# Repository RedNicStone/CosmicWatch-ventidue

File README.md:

---

# CosmicWatch Ventidue
Continuation of the original CosmicWatch project by Spencer featuring many improvements and additions.

## What's new?
CosmicWatch Ventidue's new features are plentiful so here is a quick summary:
- Flexible design that allows connecting either one or two detectors
- Built in on-silicon coincidence detection between the two modules
  - Time resolutions from 5ns down to just 1ns [cooling required]
- Powerful Teensy 4.1 microcontroller
- Full color 1.5" OLED display with great user interface
  - Rotary encoder for easy navigation
  - Buzzer for audible counting and interface feedback
  - Custom rendering library for maximum performance
- Optional solder-free support for multiple prebuilt sensor modules
  - GPS, Pressure, Humidity, Temperature and RTC supported
- Built in Ethernet module for intra & intercommunication
- Improved mechanical stability and 3D printed casing
- Interrupt driven software architecture for accurate counting and a responsive user interface

## Hardware 
A first prototype has been produced and tested. 
We are currently busy on fabricating a newer board that will be tested as soon as finished.  
There are plans to provide a kit with a pre-assembled board for purchase once hardware development has sized.

### Overview
> todo

## Software 
Software is currently undergoing heavy development and is only barely runnable.  
If you do want to take a look [check this folder](software/arduino).

The following modules have been written so far:
- Custom rendering pipeline
- OLED driver [Needs push to support DMA]
- On-chip coincidence detection
- Example for testing peripherals

The following modules still need tending:
- True type font rendering
- UI and windowing system
- Data acquisition and storage
- Ethernet communication

**Any help is much appreciated!**

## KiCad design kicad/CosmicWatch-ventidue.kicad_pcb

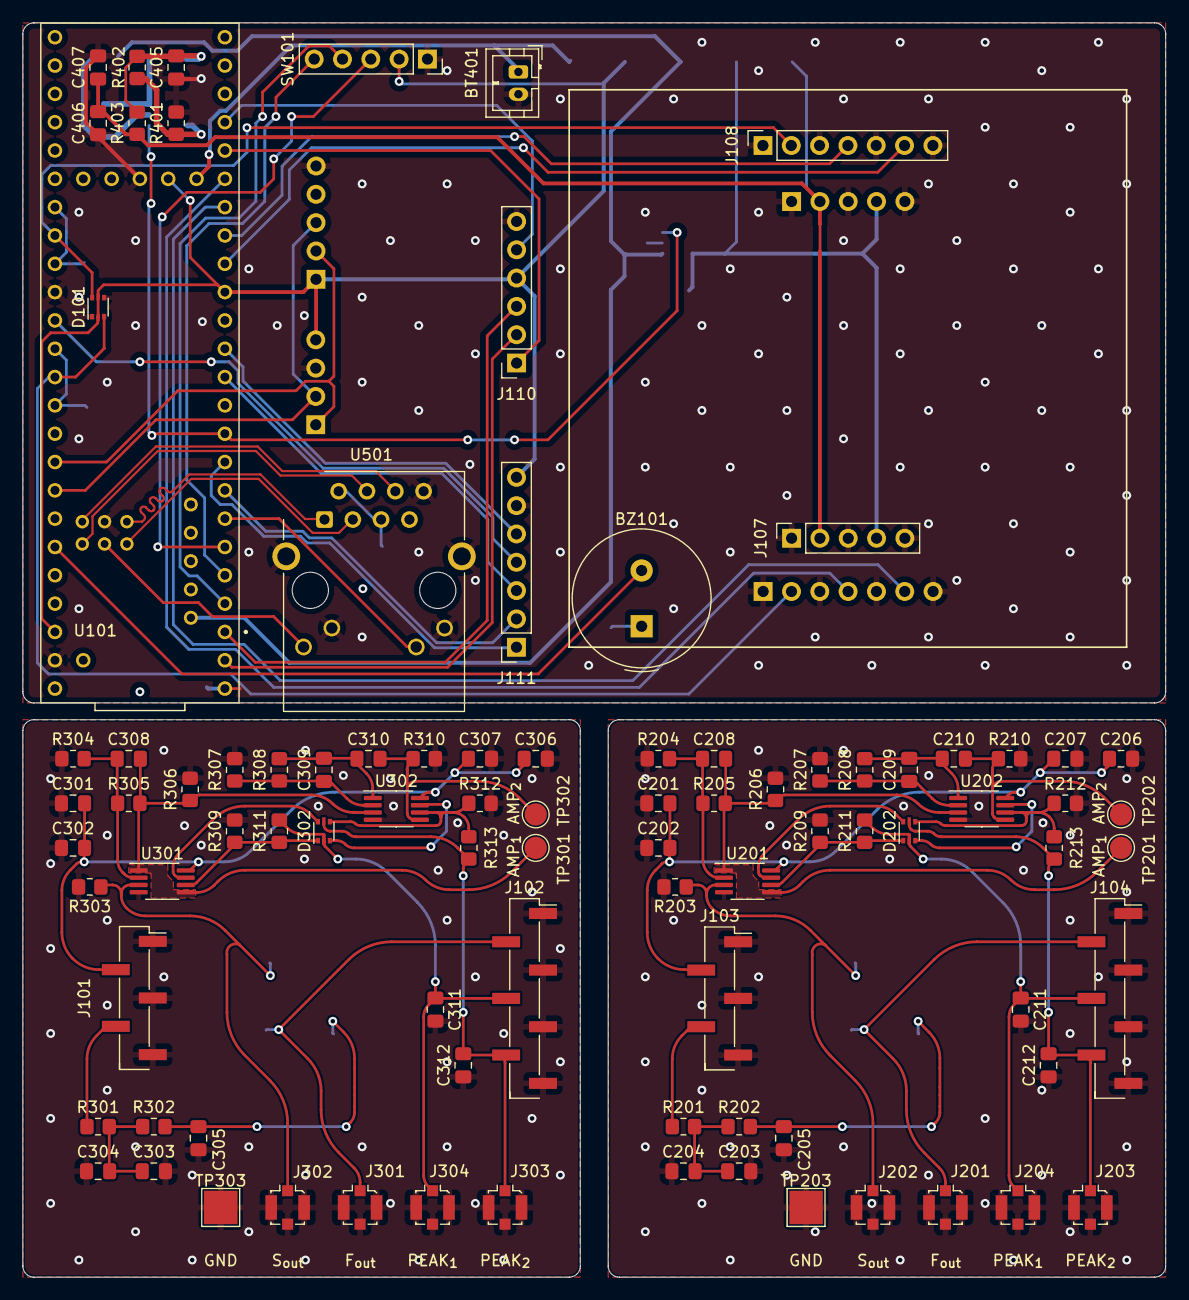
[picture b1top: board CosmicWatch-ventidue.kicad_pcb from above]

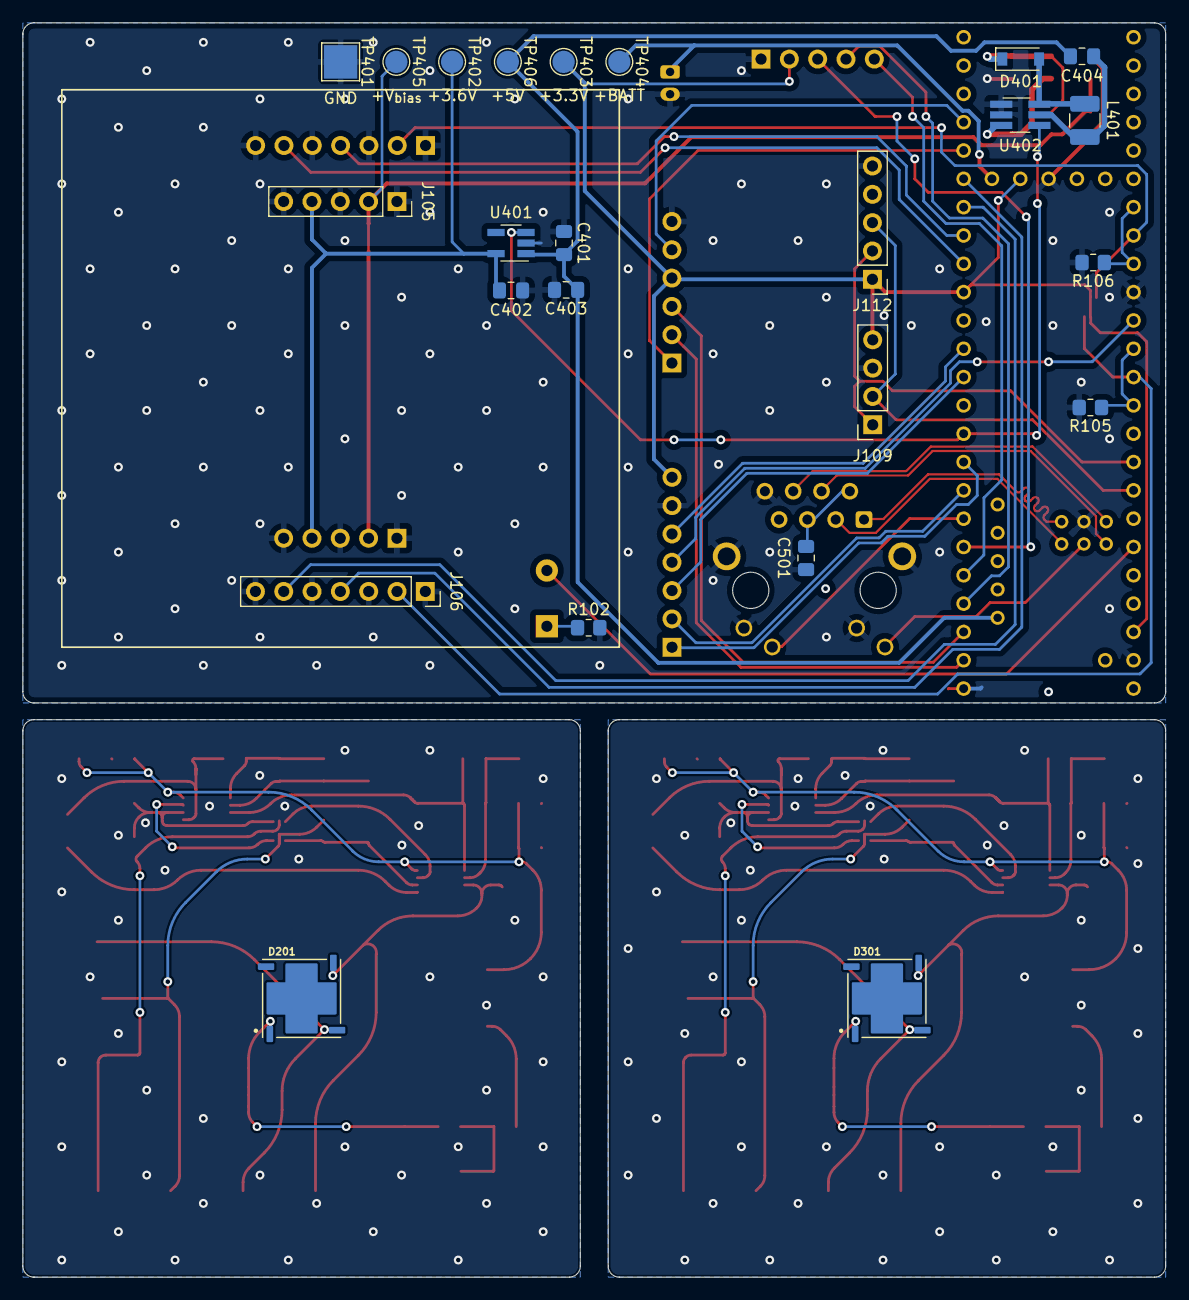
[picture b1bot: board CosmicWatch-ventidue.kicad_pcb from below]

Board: 2 copper layers, 102.5 x 112.5 mm, 114 parts (24 on the bottom side), 78 nets.

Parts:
BT401: Battery_Cell; JST_PH_B2B-PH-K_1x02_P2.00mm_Vertical
BZ101: Buzzer; Buzzer_TDK_PS1240P02BT_D12.2mm_H6.5mm
C201, C204, C205, C207, C301, C304, C305, C307, C407: 10nF; C_0805_2012Metric_Pad1.18x1.45mm_HandSolder
C202, C206, C302, C306, C501: 0.1uF; C_0805_2012Metric_Pad1.18x1.45mm_HandSolder
C203, C210, C303, C310, C401, C402, C403, C404, C405, C406: 1uF; C_0805_2012Metric_Pad1.18x1.45mm_HandSolder
C208, C209, C308, C309: 13pF; C_0805_2012Metric_Pad1.18x1.45mm_HandSolder
C211, C212, C311, C312: 2nF; C_0805_2012Metric_Pad1.18x1.45mm_HandSolder
D101, D202, D302: BAS70XY; SOT-666
D201, D301: SiPM_MICRORB−60035−MLP; SiPM_MICROFC-60035-SMT-HANDSOLDER
D401: D_Schottky; D_SOD-123
J101, J103: Conn_01x05; PinHeader_1x05_P2.54mm_Vertical_SMD_Pin1Right
J102, J104: Conn_01x07; PinHeader_1x07_P2.54mm_Vertical_SMD_Pin1Right
J105, J107: Conn_01x05; PinSocket_1x05_P2.54mm_Vertical
J106, J108: Conn_01x07; PinSocket_1x07_P2.54mm_Vertical
J109: BMP280; PinSocket_1x04_P2.54mm_Vertical
J110: Conn_01x06; PinSocket_1x06_P2.54mm_Vertical
J111: OLED; PinSocket_1x07_P2.54mm_Vertical
J112: DS3231; PinHeader_1x05_P2.54mm_Vertical
J201, J202, J203, J204, J301, J302, J303, J304: Conn_SMA; U.FL_Molex_MCRF_73412-0110_Vertical
L401: 47uH; L_1210_3225Metric_Pad1.42x2.65mm_HandSolder
R102, R208, R308: 1k; R_0805_2012Metric_Pad1.20x1.40mm_HandSolder
R105, R106, R206, R210, R306, R310: 10k; R_0805_2012Metric_Pad1.20x1.40mm_HandSolder
R201, R202, R301, R302: 50; R_0805_2012Metric_Pad1.20x1.40mm_HandSolder
R203, R303: 10; R_0805_2012Metric_Pad1.20x1.40mm_HandSolder
R204, R207, R304, R307: 150; R_0805_2012Metric_Pad1.20x1.40mm_HandSolder
R205, R305: 2.32k; R_0805_2012Metric_Pad1.20x1.40mm_HandSolder
R209, R211, R212, R213, R309, R311, R312, R313: 100k; R_0805_2012Metric_Pad1.20x1.40mm_HandSolder
R401: 6.65k; R_0805_2012Metric_Pad1.20x1.40mm_HandSolder
R402: 147k; R_0805_2012Metric_Pad1.20x1.40mm_HandSolder
R403: 100; R_0805_2012Metric_Pad1.20x1.40mm_HandSolder
SW101: Digital_Rotary_Encoder_Switch; PinSocket_1x05_P2.54mm_Vertical
TP201, TP301: AMP_{1}; TestPoint_Pad_D2.0mm
TP202, TP302: AMP_{2}; TestPoint_Pad_D2.0mm
TP203, TP303: GND; TestPoint_Pad_3.0x3.0mm
TP401: TestPoint; TestPoint_Pad_3.0x3.0mm
TP402, TP403, TP404, TP405, TP406: TestPoint; TestPoint_Pad_D2.0mm
U101: Teensy4.1
U201, U202, U301, U302: LT1807; MSOP-8_3x3mm_P0.65mm
U401: TCR2EF; SOT-23-5_HandSoldering
U402: MAX5025; TSOT-23-6_HandSoldering
U501: J1B12111CCD; RJ45_Cetus_J1B1211CCD_Horizontal

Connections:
+3.3V: D101.2 (K), D101.5 (K), J109.4, J110.4, J111.7, J112.1, SW101.2 (VCC), TP403.1, U101.3.3V_1 (3.3V), U101.3.3V_2 (3.3V__1), U101.3.3V_3 (3.3V__2)
+3.6V: C402.1, J105.4, J107.4, TP402.1, U401.5 (VOUT)
+5V: C401.1, C403.1, C404.1, TP406.1, U101.5V, U401.1 (VIN)
+BATT: BT401.1 (+), TP404.1, U101.VBAT
+V_{bias}: C406.1, C407.1, J105.2, J107.2, R403.2, TP405.1
/Buzzer: BZ101.2 (+), U101.21 (A7)
/D_{1}-F: D101.3 (common), J106.2, U101.15 (A1)
/D_{1}-P_{1}: J106.4, U101.27 (A13)
/D_{1}-P_{2}: J106.6, U101.26 (A12)
/D_{2}-F: D101.6 (common), J108.2, U101.40 (A16)
/D_{2}-P_{1}: J108.4, U101.25 (A11)
/D_{2}-P_{2}: J108.6, U101.24 (A10)
/Detector PCB 1/+3.6V: C301.1, C302.1, C306.1, C307.1, J101.2, U301.8 (V+), U302.8 (V+)
/Detector PCB 1/AMP_{1}: C308.2, R305.2, R306.1, TP301.1, U301.1, U301.5 (+), U302.3 (+)
/Detector PCB 1/AMP_{2}: C310.2, R310.1, TP302.1, U302.5 (+)
/Detector PCB 1/F_{out}: D301.2 (Fast_Output), J102.2, J301.1 (In)
/Detector PCB 1/GND: C301.2, C302.2, C303.2, C304.2, C305.2, C306.2, C307.2, C311.2, C312.2, J101.1, J101.3, J101.5, J102.1, J102.3, J102.5, J102.7, J301.2 (Ext), J302.2 (Ext), J303.2 (Ext), J304.2 (Ext), R303.2, R304.2, R306.2, R307.2, R309.2, R310.2, R312.2, TP303.1, U301.4 (V-), U302.4 (V-)
/Detector PCB 1/PEAK_{1}: C311.1, D302.2 (K), J102.4, J304.1 (In), R311.2
/Detector PCB 1/PEAK_{2}: C312.1, D302.5 (K), J102.6, J303.1 (In), R313.2
/Detector PCB 1/S_{out}: D301.3 (Cathode), J302.1 (In), R303.1, U301.3 (+)
/Detector PCB 1/V_{bias}: J101.4, R301.1
/Detector PCB 2/+3.6V: C201.1, C202.1, C206.1, C207.1, J103.2, U201.8 (V+), U202.8 (V+)
/Detector PCB 2/AMP_{1}: C208.2, R205.2, R206.1, TP201.1, U201.1, U201.5 (+), U202.3 (+)
/Detector PCB 2/AMP_{2}: C210.2, R210.1, TP202.1, U202.5 (+)
/Detector PCB 2/F_{out}: D201.2 (Fast_Output), J104.2, J201.1 (In)
/Detector PCB 2/GND: C201.2, C202.2, C203.2, C204.2, C205.2, C206.2, C207.2, C211.2, C212.2, J103.1, J103.3, J103.5, J104.1, J104.3, J104.5, J104.7, J201.2 (Ext), J202.2 (Ext), J203.2 (Ext), J204.2 (Ext), R203.2, R204.2, R206.2, R207.2, R209.2, R210.2, R212.2, TP203.1, U201.4 (V-), U202.4 (V-)
/Detector PCB 2/PEAK_{1}: C211.1, D202.2 (K), J104.4, J204.1 (In), R211.2
/Detector PCB 2/PEAK_{2}: C212.1, D202.5 (K), J104.6, J203.1 (In), R213.2
/Detector PCB 2/S_{out}: D201.3 (Cathode), J202.1 (In), R203.1, U201.3 (+)
/Detector PCB 2/V_{bias}: J103.4, R201.1
/Eth-LED_{1}: U101.LED, U501.9 (LLED+)
/Eth-LED_{2}: U101.5 (IN2), U501.11 (RLED+)
/Eth-RX+: U101.R+, U501.4 (TD-)
/Eth-RX-: U101.R-, U501.6 (TD+)
/Eth-TX+: U101.T+, U501.1 (RD-)
/Eth-TX-: U101.T-, U501.3 (RD+)
/GPS-EN: J110.1, U101.28 (RX7)
/GPS-PPS: J110.5, U101.29 (TX7)
/GPS-RX: J110.2, U101.0 (RX1)
/GPS-TX: J110.3, U101.1 (TX1)
/I^{2}C-SCL: J109.2, J112.3, U101.19 (A5)
/I^{2}C-SDA: J109.1, J112.2, U101.18 (A4)
/OLED-DC: J111.2, U101.6 (OUT1D)
/OLED-RST: J111.1, U101.7 (RX2)
/PWR-~SHDN: U101.8 (TX2), U401.3 (CE), U402.4 (~SHDN)
/Rot-BTN: SW101.3 (SW), U101.4 (BCLK2)
/Rot-IL: SW101.5 (CLK), U101.3 (LRCLK2)
/Rot-IR: SW101.4 (DT), U101.2 (OUT2)
/SPI-CLK: J111.4, U101.13 (SCK)
/SPI-CS_{1}: J111.3, U101.10 (CS1)
/SPI-M_{O}S_{I}: J111.5, U101.11 (MOSI)
GND: BT401.2 (-), C401.2, C402.2, C403.2, C405.2, C406.2, C407.2, C501.2, D101.1 (A), D101.4 (A), J105.1, J105.3, J105.5, J106.1, J106.3, J106.5, J106.7, J107.1, J107.3, J107.5, J108.1, J108.3, J108.5, J108.7, J109.3, J110.6, J111.6, J112.5, R102.2, R105.2, R106.2, R401.1, SW101.1 (GND), TP401.1, U101.GND1 (GND), U101.GND2 (GND__1), U101.GND3 (GND__2), U101.GND4 (GND__3), U101.GND5 (GND__4), U401.2 (GND), U402.1 (PGND), U402.2 (GND), U501.8, U501.10 (LLED-), U501.12 (RLED-), U501.13 (SHIELD)
unnamed: BZ101.1 (-), R102.1
unnamed: C203.1, C204.1, R201.2, R202.1
unnamed: C205.1, D201.1 (Annode), R202.2
unnamed: C208.1, R204.1, R205.1, U201.2 (-)
unnamed: C209.1, R207.1, R208.1, U202.2 (-)
unnamed: C209.2, C210.1, R208.2, U202.1
unnamed: C303.1, C304.1, R301.2, R302.1
unnamed: C305.1, D301.1 (Annode), R302.2
unnamed: C308.1, R304.1, R305.1, U301.2 (-)
unnamed: C309.1, R307.1, R308.1, U302.2 (-)
unnamed: C309.2, C310.1, R308.2, U302.1
unnamed: C404.2, L401.1, U402.5 (VIN)
unnamed: C405.1, D401.1 (K), R402.2, R403.1
unnamed: C501.1, U501.2 (CT), U501.5 (CT)
unnamed: D202.1 (A), R209.1, R211.1, U201.6 (-)
unnamed: D202.3 (common), U202.7
unnamed: D202.4 (A), R212.1, R213.1, U202.6 (-)
unnamed: D202.6 (common), U201.7
unnamed: D302.1 (A), R309.1, R311.1, U301.6 (-)
unnamed: D302.3 (common), U302.7
unnamed: D302.4 (A), R312.1, R313.1, U302.6 (-)
unnamed: D302.6 (common), U301.7
unnamed: D401.2 (A), L401.2, U402.6 (LX)
unnamed: R105.1, U101.14 (A0), U101.16 (A2)
unnamed: R106.1, U101.39 (A15), U101.41 (A17)
unnamed: R401.2, R402.1, U402.3 (FB)

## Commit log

2022-07-28 Version 2.3 commit
2022-07-29 Added gerber files in kicad/plots, both compressed and uncompressed
2022-08-02 Updated PCB files and added plots
2022-08-02 Updated software package
2022-08-17 Push to version 3.3
2022-09-05 Updated PCB Images
2022-09-05 Updated README.md, still a todo
2022-09-05 Foreign CSS contained in SVGs for the readme, GitHub does not allow CSS in Readmes
2022-09-05 Updated KiCAD plots
2022-09-05 Removed CMAKE build data
2022-09-05 Removed absolute path in CMAKE file
2022-09-05 Updated demo to newer API version
2022-09-05 Removed unnecessary .cpp file
2022-09-05 Updated file writer for new API
2022-09-05 Vector native data handle support
2022-09-05 Some generic include fixes
2022-09-05 New style object, to be expanded
2022-09-05 New widget API and first widget, a button
2022-09-05 New plot files
2022-09-09 New text renderer. New SiPM footprint. Included c++20 compiler.
